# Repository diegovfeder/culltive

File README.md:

<h1 align="center">
    Culltive
</h1>

<h4 align="center">
  Culltive is a startup that combines technology, nature and decoration.
</h4>

<p align="center">
    <a href="#-Project">Project</a>&nbsp;&nbsp;&nbsp;|&nbsp;&nbsp;&nbsp;
    <a href="#rocket-Technology">Technology</a>&nbsp;&nbsp;&nbsp;
</p>

<br>

## 💻 Project

It was developed to solve the difficulties of maintaining gardens in urban environments, taking into account unfavorable spaces and the lack of time for the necessary care. 

## :rocket: Technology

This project was developed with the following technologies:

- [React](https://reactjs.org)
- [React Native](https://facebook.github.io/react-native/)
- [Expo](https://expo.io/)
- [Firebase](https://firebase.google.com/)
- [Platform.io](https://platformio.org/)

---
Startup engineered by Diego Feder

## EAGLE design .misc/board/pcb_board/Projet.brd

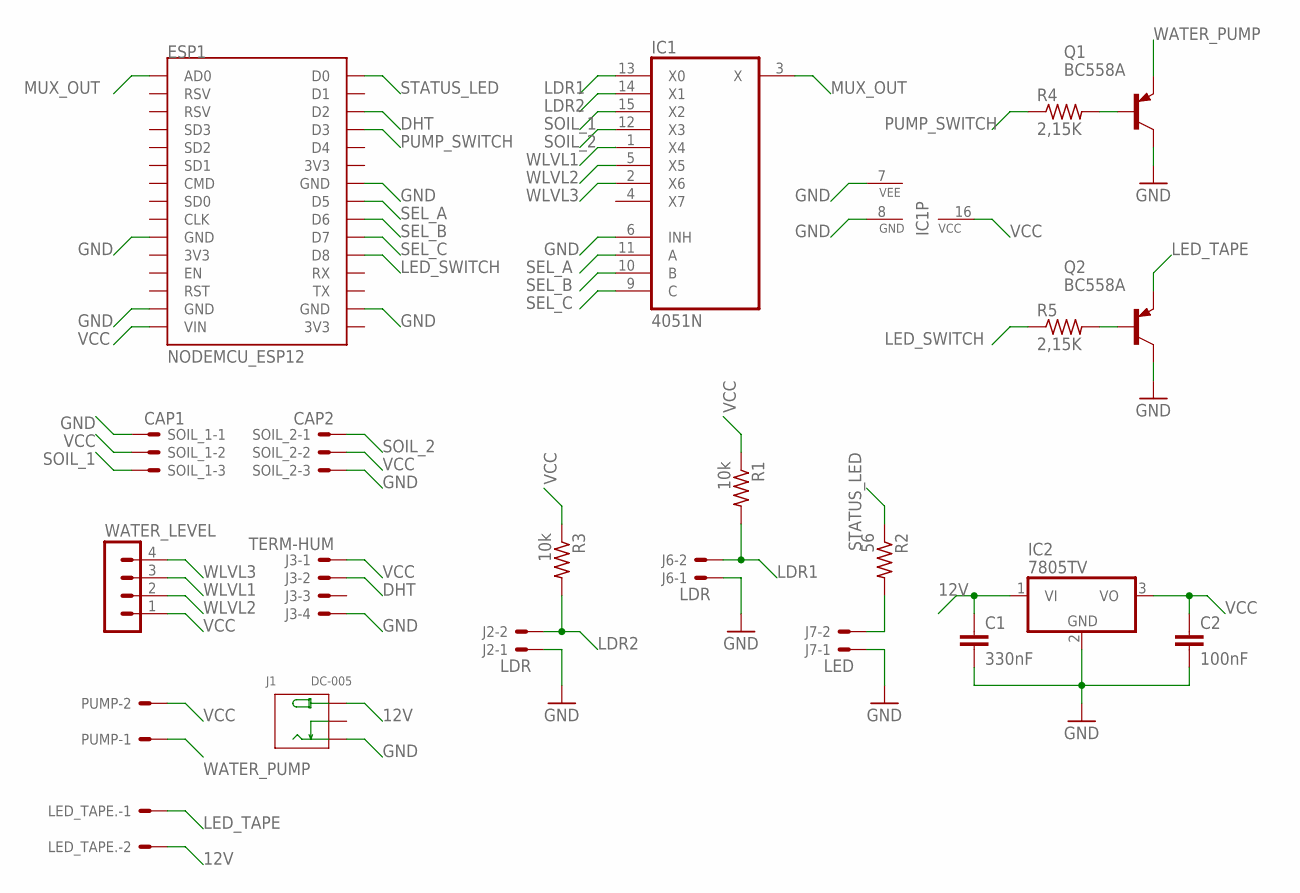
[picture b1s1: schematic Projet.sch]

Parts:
C1: 330nF; CAP_CERAMICO
C2: 100nF; CAP_CERAMICO
ESP1: NODEMCU_ESP12
IC1: 4051N; DIL16
IC2: 7805TV; TO220V
J1: DC-005; DCJ3P-14.2X11.0X9.0MM
J2, J6: LDR; 7395-02
J3: TERM-HUM; 7395-04
J7: LED; 7395-02
LED_TAPE.: KK-156-2
PUMP: KK-156-2
Q1, Q2: BC558A; TO92-EBC
R1, R3: 10k; 0204/7
R2: 56; 0204/7
R4, R5: 2,15K; 0204/7
SOIL_1: CAP1; 7395-03
SOIL_2: CAP2; 7395-03
WATER_LEVEL: MA04-1

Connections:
12V: C1.P$1 (1), IC2.1 (VI), J1.+, LED_TAPE..2
DHT: ESP1.D2, J3.2
GND: C1.P$2 (2), C2.P$2 (2), ESP1.GND@0 (GND), ESP1.GND@1 (GND), ESP1.GND@2 (GND), ESP1.GND@3 (GND), IC1.6 (INH), IC1.7 (VEE), IC1.8 (GND), IC2.2 (GND), J1.-1 (-), J2.1, J3.4, J6.1, J7.1, Q1.C, Q2.C, SOIL_1.1, SOIL_2.3
LDR1: IC1.13 (X0), J6.2, R1.2
LDR2: IC1.14 (X1), J2.2, R3.2
LED_SWITCH: ESP1.D8, R5.1
LED_TAPE: LED_TAPE..1, Q2.E
MUX_OUT: ESP1.AD0, IC1.3 (X)
unnamed: J7.2, R2.2
unnamed: Q1.B, R4.2
unnamed: Q2.B, R5.2
PUMP_SWITCH: ESP1.D3, R4.1
SEL_A: ESP1.D5, IC1.11 (A)
SEL_B: ESP1.D6, IC1.10 (B)
SEL_C: ESP1.D7, IC1.9 (C)
SOIL_1: IC1.15 (X2), SOIL_1.3
SOIL_2: IC1.12 (X3), SOIL_2.1
STATUS_LED: ESP1.D0, R2.1
VCC: C2.P$1 (1), ESP1.VIN, IC1.16 (VCC), IC2.3 (VO), J3.1, PUMP.2, R1.1, R3.1, SOIL_1.2, SOIL_2.2, WATER_LEVEL.1
WATER_PUMP: PUMP.1, Q1.E
WLVL1: IC1.1 (X4), WATER_LEVEL.3
WLVL2: IC1.5 (X5), WATER_LEVEL.2
WLVL3: IC1.2 (X6), WATER_LEVEL.4

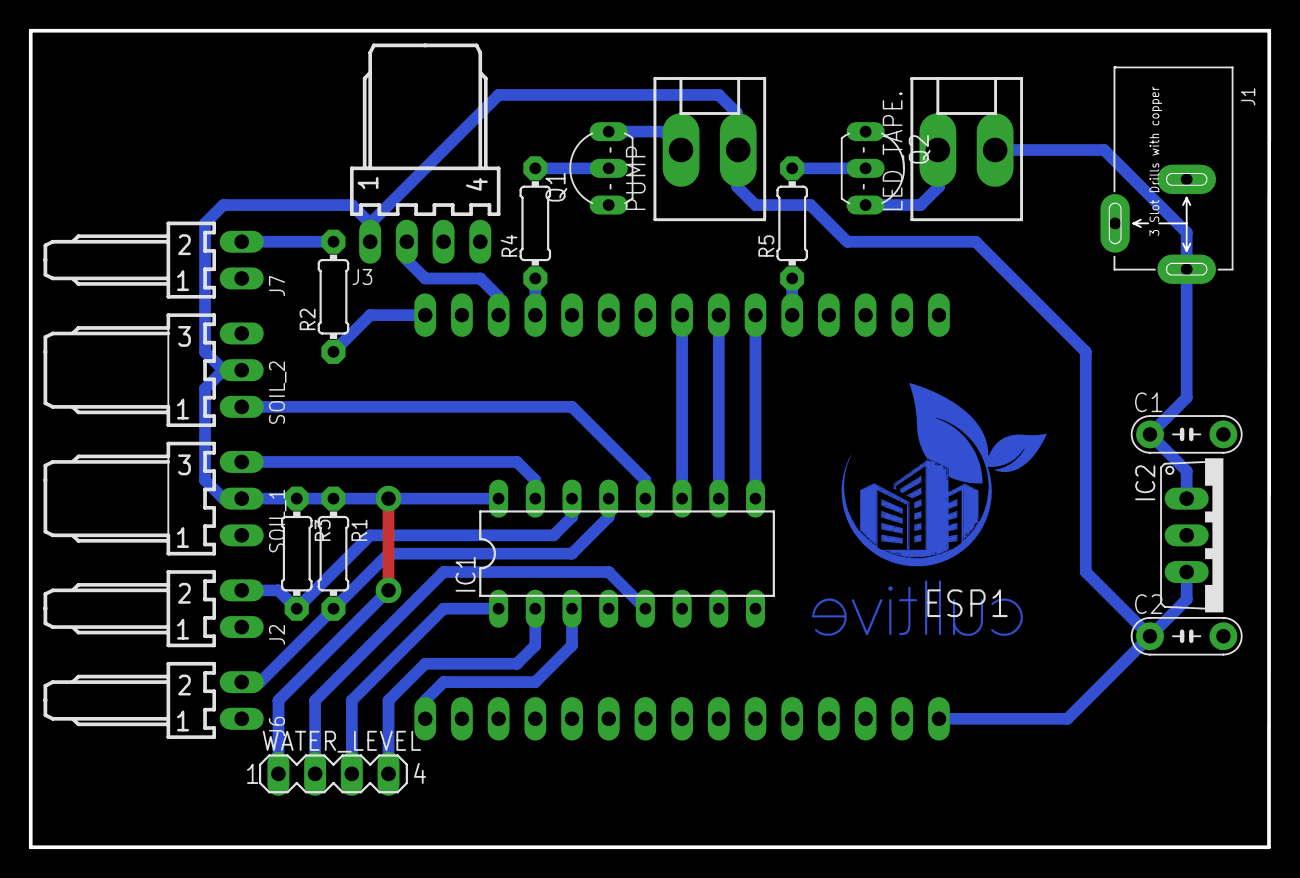
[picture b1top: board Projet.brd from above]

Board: 2 copper layers, 85.7 x 56.5 mm, 22 parts (0 on the bottom side), 23 nets.

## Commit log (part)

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2020-04-17 Expo App Commit
2020-04-17 haha
2020-04-20 Expo App
2020-04-21 Re-base added
2020-04-24 Started Editing settingsScreen
2020-04-24 UI Finished
2020-05-01 refactor (typescript) project initiation
2020-05-05 add to package.json and styles.tsx
2020-05-05 Add HomeScreen and Drawer
    fix Drawer Navigator button (navigate.toggleDrawer())
    fix Settings
    fix Drawer memory leak warning
    start AsyncStorage verification if app has already paired with a device
    - firsttime: Go to PairScreen (Ask for Permissions)
    - paired dvc: fetch data or pick a plant
2020-05-05 update @types package.json
    na
2020-05-06 feat(Report) add CardView UI
    Added new UI elements to Report.tsx:
    - todo: get data from Firebase
    - todo: get weatherAPI data
    - todo: card onClick goes to Chart Screen respectively
    - todo: add Icons
    - fix: UI colors
2020-05-06 feat(PairNavigator) simplify and clean app flow
    - fix: react navigation is buggy // study and go
2020-05-08 Hope this works
    ...yup
2020-05-11 feat (IOT Pair Device) uncompleted
2020-05-12 feat (sendData) axios sending data to iot device
2020-05-12 fix (Android Device)
2020-05-19 something went wrong...
2020-05-23 new commit
    nice bro!
2020-05-25 Getting this thing going ;)
2020-05-27 WelcomeScreen // Terms // Drawer Navigation (fixing...)
2020-05-27 still fixing DrawerNavigator
2020-06-01 Fixing commit
2020-06-24 getting back to those commitsssss
2020-06-30 Report.tsx is now getting lastReading from firestore and posting values to MyCarousel
2020-07-02 General Refactor
2020-07-03 Feature: postDevice verification handleSuccess
2020-07-04 decodedToken / fbAuth returns email for req.user.email signin // drawer gets user email and present as custom header
2020-07-10 Restructuring Context API
2020-07-16 Organized cloud-functions and developing deviceActions
2020-07-20 some other stuff...
2020-07-21 little refactor and some design changes
2020-07-21 Bump lodash from 4.17.15 to 4.17.19 in /cloud-functions/functions
    Bumps [lodash](https://github.com/lodash/lodash) from 4.17.15 to 4.17.19.
    - [Release notes](https://github.com/lodash/lodash/releases)
    - [Commits](https://github.com/lodash/lodash/compare/4.17.15...4.17.19)
2020-07-21 Bump lodash from 4.17.15 to 4.17.19 in /AppCulltive
    Bumps [lodash](https://github.com/lodash/lodash) from 4.17.15 to 4.17.19.
    - [Release notes](https://github.com/lodash/lodash/releases)
    - [Commits](https://github.com/lodash/lodash/compare/4.17.15...4.17.19)
2020-07-21 Bump lodash from 4.17.15 to 4.17.19 in /expo-app
    Bumps [lodash](https://github.com/lodash/lodash) from 4.17.15 to 4.17.19.
    - [Release notes](https://github.com/lodash/lodash/releases)
    - [Commits](https://github.com/lodash/lodash/compare/4.17.15...4.17.19)
2020-07-22 Feature: E-mail Reset - needs validation & testing
2020-08-03 I guess this works
2020-08-27 another commit
2021-01-06 Bump axios from 0.19.2 to 0.21.1 in /AppCulltive
    Bumps [axios](https://github.com/axios/axios) from 0.19.2 to 0.21.1.
    - [Release notes](https://github.com/axios/axios/releases)
    - [Changelog](https://github.com/axios/axios/blob/v0.21.1/CHANGELOG.md)
    - [Commits](https://github.com/axios/axios/compare/v0.19.2...v0.21.1)
2021-02-08 Bump websocket-extensions from 0.1.3 to 0.1.4 in /expo-app
    Bumps [websocket-extensions](https://github.com/faye/websocket-extensions-node) from 0.1.3 to 0.1.4.
    - [Release notes](https://github.com/faye/websocket-extensions-node/releases)
    - [Changelog](https://github.com/faye/websocket-extensions-node/blob/master/CHANGELOG.md)
    - [Commits](https://github.com/faye/websocket-extensions-node/compare/0.1.3...0.1.4)
2021-02-09 Bump lodash from 4.17.15 to 4.17.20 in /expo-app
    Bumps [lodash](https://github.com/lodash/lodash) from 4.17.15 to 4.17.20.
    - [Release notes](https://github.com/lodash/lodash/releases)
    - [Commits](https://github.com/lodash/lodash/compare/4.17.15...4.17.20)
2021-02-09 Bump websocket-extensions from 0.1.3 to 0.1.4 in /AppCulltive
    Bumps [websocket-extensions](https://github.com/faye/websocket-extensions-node) from 0.1.3 to 0.1.4.
    - [Release notes](https://github.com/faye/websocket-extensions-node/releases)
    - [Changelog](https://github.com/faye/websocket-extensions-node/blob/master/CHANGELOG.md)
    - [Commits](https://github.com/faye/websocket-extensions-node/compare/0.1.3...0.1.4)
2021-02-13 Bump axios from 0.19.2 to 0.21.1 in /expo-app
    Bumps [axios](https://github.com/axios/axios) from 0.19.2 to 0.21.1.
    - [Release notes](https://github.com/axios/axios/releases)
    - [Changelog](https://github.com/axios/axios/blob/v0.21.1/CHANGELOG.md)
    - [Commits](https://github.com/axios/axios/compare/v0.19.2...v0.21.1)
2021-02-13 Bump axios from 0.19.2 to 0.21.1 in /react-dashboard
    Bumps [axios](https://github.com/axios/axios) from 0.19.2 to 0.21.1.
    - [Release notes](https://github.com/axios/axios/releases)
    - [Changelog](https://github.com/axios/axios/blob/master/CHANGELOG.md)
    - [Commits](https://github.com/axios/axios/compare/v0.19.2...v0.21.1)
2021-05-06 Bump property-expr from 2.0.2 to 2.0.4 in /AppCulltive
    Bumps [property-expr](https://github.com/jquense/expr) from 2.0.2 to 2.0.4.
    - [Release notes](https://github.com/jquense/expr/releases)
    - [Changelog](https://github.com/jquense/expr/blob/master/CHANGELOG.md)
    - [Commits](https://github.com/jquense/expr/compare/v2.0.2...v2.0.4)
2021-05-08 Bump ua-parser-js from 0.7.21 to 0.7.28 in /expo-app
    Bumps [ua-parser-js](https://github.com/faisalman/ua-parser-js) from 0.7.21 to 0.7.28.
    - [Release notes](https://github.com/faisalman/ua-parser-js/releases)
    - [Commits](https://github.com/faisalman/ua-parser-js/compare/0.7.21...0.7.28)
2021-05-08 Bump ua-parser-js from 0.7.21 to 0.7.28 in /AppCulltive
    Bumps [ua-parser-js](https://github.com/faisalman/ua-parser-js) from 0.7.21 to 0.7.28.
    - [Release notes](https://github.com/faisalman/ua-parser-js/releases)
    - [Commits](https://github.com/faisalman/ua-parser-js/compare/0.7.21...0.7.28)
2021-05-11 Bump lodash from 4.17.20 to 4.17.21 in /AppCulltive
    Bumps [lodash](https://github.com/lodash/lodash) from 4.17.20 to 4.17.21.
    - [Release notes](https://github.com/lodash/lodash/releases)
    - [Commits](https://github.com/lodash/lodash/compare/4.17.20...4.17.21)
2021-05-11 Bump lodash from 4.17.20 to 4.17.21 in /expo-app
    Bumps [lodash](https://github.com/lodash/lodash) from 4.17.20 to 4.17.21.
    - [Release notes](https://github.com/lodash/lodash/releases)
    - [Commits](https://github.com/lodash/lodash/compare/4.17.20...4.17.21)
2021-05-11 Bump lodash from 4.17.19 to 4.17.21 in /cloud-functions/functions
    Bumps [lodash](https://github.com/lodash/lodash) from 4.17.19 to 4.17.21.
    - [Release notes](https://github.com/lodash/lodash/releases)
    - [Commits](https://github.com/lodash/lodash/compare/4.17.19...4.17.21)
2021-05-11 Bump hosted-git-info from 2.8.8 to 2.8.9 in /expo-app
    Bumps [hosted-git-info](https://github.com/npm/hosted-git-info) from 2.8.8 to 2.8.9.
    - [Release notes](https://github.com/npm/hosted-git-info/releases)
    - [Changelog](https://github.com/npm/hosted-git-info/blob/v2.8.9/CHANGELOG.md)
    - [Commits](https://github.com/npm/hosted-git-info/compare/v2.8.8...v2.8.9)
2021-05-12 Bump nodemailer from 6.4.10 to 6.4.16 in /cloud-functions/functions
    Bumps [nodemailer](https://github.com/nodemailer/nodemailer) from 6.4.10 to 6.4.16.
    - [Release notes](https://github.com/nodemailer/nodemailer/releases)
    - [Changelog](https://github.com/nodemailer/nodemailer/blob/master/CHANGELOG.md)
    - [Commits](https://github.com/nodemailer/nodemailer/compare/v6.4.10...v6.4.16)
2021-05-26 Bump browserslist from 4.11.1 to 4.16.6 in /expo-app
    Bumps [browserslist](https://github.com/browserslist/browserslist) from 4.11.1 to 4.16.6.
    - [Release notes](https://github.com/browserslist/browserslist/releases)
    - [Changelog](https://github.com/browserslist/browserslist/blob/main/CHANGELOG.md)
    - [Commits](https://github.com/browserslist/browserslist/compare/4.11.1...4.16.6)
2021-06-08 Bump merge-deep from 3.0.2 to 3.0.3 in /expo-app
    Bumps [merge-deep](https://github.com/jonschlinkert/merge-deep) from 3.0.2 to 3.0.3.
    - [Release notes](https://github.com/jonschlinkert/merge-deep/releases)
    - [Commits](https://github.com/jonschlinkert/merge-deep/compare/3.0.2...3.0.3)
    ---
    updated-dependencies:
    - dependency-name: merge-deep
2021-06-12 Bump glob-parent from 5.1.1 to 5.1.2 in /AppCulltive
    Bumps [glob-parent](https://github.com/gulpjs/glob-parent) from 5.1.1 to 5.1.2.
    - [Release notes](https://github.com/gulpjs/glob-parent/releases)
    - [Changelog](https://github.com/gulpjs/glob-parent/blob/main/CHANGELOG.md)
    - [Commits](https://github.com/gulpjs/glob-parent/compare/v5.1.1...v5.1.2)
    ---
    updated-dependencies:
2021-07-20 Bump react-native from 0.62.2 to 0.62.3 in /AppCulltive
    Bumps [react-native](https://github.com/facebook/react-native) from 0.62.2 to 0.62.3.
    - [Release notes](https://github.com/facebook/react-native/releases)
    - [Changelog](https://github.com/facebook/react-native/blob/main/Releases.md)
    - [Commits](https://github.com/facebook/react-native/compare/v0.62.2...v0.62.3)
    ---
    updated-dependencies:
2021-08-05 Bump tar from 4.4.13 to 4.4.15 in /expo-app
    Bumps [tar](https://github.com/npm/node-tar) from 4.4.13 to 4.4.15.
    - [Release notes](https://github.com/npm/node-tar/releases)
    - [Changelog](https://github.com/npm/node-tar/blob/main/CHANGELOG.md)
    - [Commits](https://github.com/npm/node-tar/compare/v4.4.13...v4.4.15)
    ---
    updated-dependencies:
2021-08-12 Bump path-parse from 1.0.6 to 1.0.7 in /expo-app
    Bumps [path-parse](https://github.com/jbgutierrez/path-parse) from 1.0.6 to 1.0.7.
    - [Release notes](https://github.com/jbgutierrez/path-parse/releases)
    - [Commits](https://github.com/jbgutierrez/path-parse/commits/v1.0.7)
    ---
    updated-dependencies:
    - dependency-name: path-parse
2021-09-02 Bump tar from 4.4.13 to 4.4.19 in /expo-app
    Bumps [tar](https://github.com/npm/node-tar) from 4.4.13 to 4.4.19.
    - [Release notes](https://github.com/npm/node-tar/releases)
    - [Changelog](https://github.com/npm/node-tar/blob/main/CHANGELOG.md)
    - [Commits](https://github.com/npm/node-tar/compare/v4.4.13...v4.4.19)
    ---
    updated-dependencies:
2021-09-02 Bump color-string from 1.5.3 to 1.6.0 in /react-dashboard
    Bumps [color-string](https://github.com/Qix-/color-string) from 1.5.3 to 1.6.0.
    - [Release notes](https://github.com/Qix-/color-string/releases)
    - [Changelog](https://github.com/Qix-/color-string/blob/master/CHANGELOG.md)
    - [Commits](https://github.com/Qix-/color-string/commits/1.6.0)
    ---
    updated-dependencies:
2021-09-02 Bump dns-packet from 1.3.1 to 1.3.4 in /react-dashboard
    Bumps [dns-packet](https://github.com/mafintosh/dns-packet) from 1.3.1 to 1.3.4.
    - [Release notes](https://github.com/mafintosh/dns-packet/releases)
    - [Changelog](https://github.com/mafintosh/dns-packet/blob/master/CHANGELOG.md)
    - [Commits](https://github.com/mafintosh/dns-packet/compare/v1.3.1...v1.3.4)
    ---
    updated-dependencies:
2021-09-02 Bump url-parse from 1.4.7 to 1.5.3 in /react-dashboard
    Bumps [url-parse](https://github.com/unshiftio/url-parse) from 1.4.7 to 1.5.3.
    - [Release notes](https://github.com/unshiftio/url-parse/releases)
    - [Commits](https://github.com/unshiftio/url-parse/compare/1.4.7...1.5.3)
    ---
    updated-dependencies:
    - dependency-name: url-parse
